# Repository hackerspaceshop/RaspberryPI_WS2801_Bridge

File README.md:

RaspberryPI_WS2801_Bridge
=========================

Software for Raspberry PI to WS2801 Bridge 
/pcb  folder includes latest schematic and baord file (eagle)  + pdf
/software includes all the raspberry pi software
/image contains one big image file that you can directly dd to an SD card (min 4GB)

http://www.hackerspaceshop.com/ledstrips/raspberrypi-ws2801.html

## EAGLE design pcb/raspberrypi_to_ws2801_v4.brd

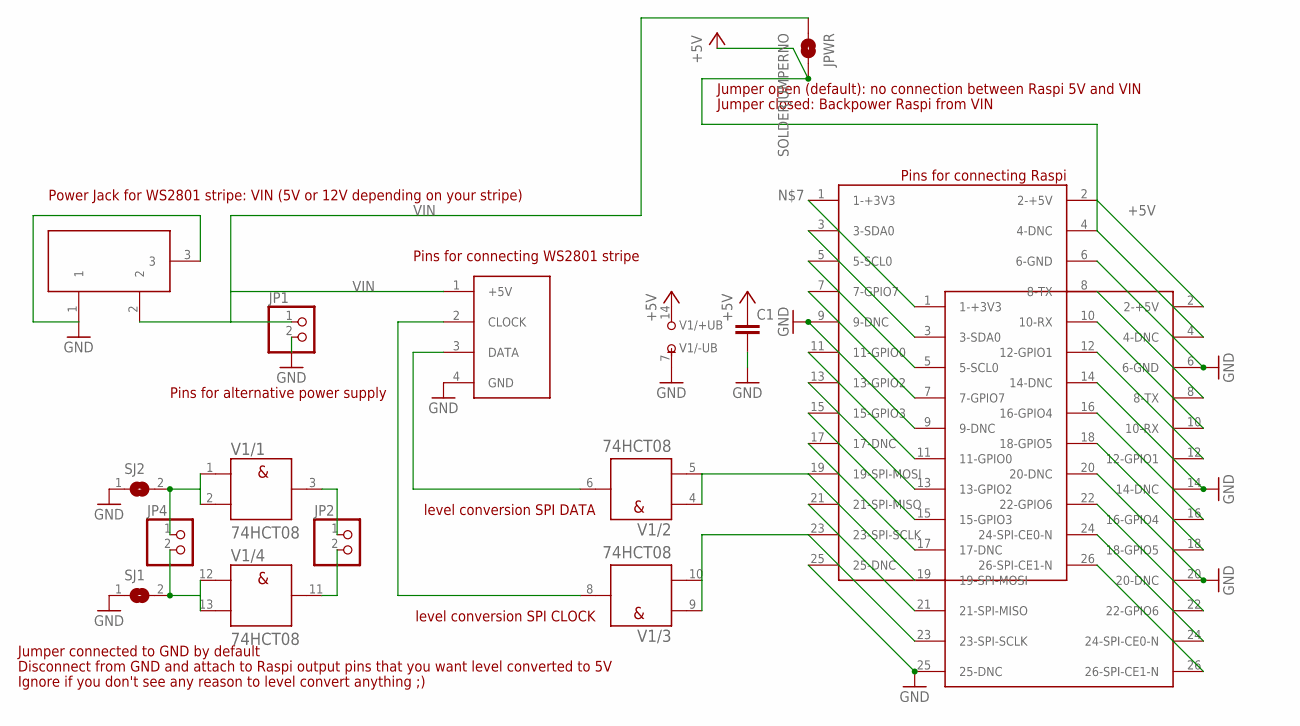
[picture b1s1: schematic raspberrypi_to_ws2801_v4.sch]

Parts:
C1: C-EU025-024X044; C025-024X044
JP1, JP2, JP4: PINHD-1X2; 1X02
JPWR: SOLDERJUMPERNO; SJ_2S-NO
SJ1, SJ2: SJ
U$1, U$2: RASPBERRY-PI
U$3: W2801STRIP; 1X04
U$5: DC21MMX; DC-21MM
V1: 74HCT08; DIL14

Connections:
+5V: C1.1, JPWR.2, U$1.2 (2-+5V), U$1.4 (4-DNC), U$2.2 (2-+5V), U$2.4 (4-DNC), V1.14 (+UB)
GND: C1.2, JP1.2, SJ1.1, SJ2.1, U$1.6 (6-GND), U$1.9 (9-DNC), U$1.14 (14-DNC), U$1.20 (20-DNC), U$1.25 (25-DNC), U$2.6 (6-GND), U$2.9 (9-DNC), U$2.14 (14-DNC), U$2.20 (20-DNC), U$2.25 (25-DNC), U$3.4 (GND), U$5.1, U$5.3, V1.7 (-UB)
unnamed: U$1.19 (19-SPI-MOSI), U$2.19 (19-SPI-MOSI), V1.4 (A), V1.5 (B)
unnamed: U$3.2 (CLOCK), V1.8 (Y)
unnamed: U$1.23 (23-SPI-SCLK), U$2.23 (23-SPI-SCLK), V1.9 (A), V1.10 (B)
unnamed: U$1.3 (3-SDA0), U$2.3 (3-SDA0)
unnamed: U$1.5 (5-SCL0), U$2.5 (5-SCL0)
unnamed: U$1.1 (1-+3V3), U$2.1 (1-+3V3)
unnamed: U$1.7 (7-GPIO7), U$2.7 (7-GPIO7)
unnamed: U$1.8 (8-TX), U$2.8 (8-TX)
unnamed: U$1.10 (10-RX), U$2.10 (10-RX)
unnamed: U$1.11 (11-GPIO0), U$2.11 (11-GPIO0)
unnamed: U$1.12 (12-GPIO1), U$2.12 (12-GPIO1)
unnamed: U$1.13 (13-GPIO2), U$2.13 (13-GPIO2)
unnamed: U$1.15 (15-GPIO3), U$2.15 (15-GPIO3)
unnamed: U$1.16 (16-GPIO4), U$2.16 (16-GPIO4)
unnamed: U$1.17 (17-DNC), U$2.17 (17-DNC)
unnamed: U$1.18 (18-GPIO5), U$2.18 (18-GPIO5)
unnamed: U$1.21 (21-SPI-MISO), U$2.21 (21-SPI-MISO)
unnamed: U$1.22 (22-GPIO6), U$2.22 (22-GPIO6)
unnamed: U$1.24 (24-SPI-CE0-N), U$2.24 (24-SPI-CE0-N)
unnamed: U$1.26 (26-SPI-CE1-N), U$2.26 (26-SPI-CE1-N)
unnamed: U$3.3 (DATA), V1.6 (Y)
unnamed: JP2.1, V1.3 (Y)
unnamed: JP2.2, V1.11 (Y)
unnamed: JP4.2, SJ1.2, V1.12 (A), V1.13 (B)
unnamed: JP4.1, SJ2.2, V1.1 (A), V1.2 (B)
VIN: JP1.1, JPWR.1, U$3.1 (+5V), U$5.2

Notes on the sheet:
Jumper connected to GND by default
Jumper open (default): no connection between Raspi 5V and VIN
Power Jack for WS2801 stripe: VIN (5V or 12V depending on your stripe)
Disconnect from GND and attach to Raspi output pins that you want level converted to 5V
Jumper closed: Backpower Raspi from VIN
Pins for alternative power supply
Pins for connecting WS2801 stripe
Pins for connecting Raspi
level conversion SPI DATA
level conversion SPI CLOCK
Ignore if you don't see any reason to level convert anything ;)

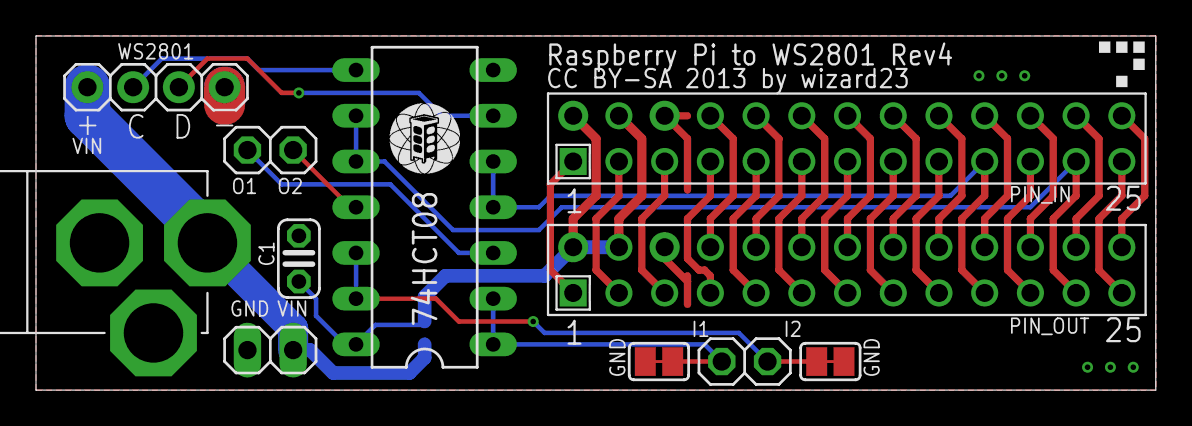
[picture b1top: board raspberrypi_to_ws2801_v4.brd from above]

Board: 2 copper layers, 62.2 x 19.7 mm, 13 parts (1 on the bottom side), 28 nets.

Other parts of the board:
U$4: METALAB_SMALL

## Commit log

2013-03-19 Wrote initial library and demo
2013-03-22 added scematic and pcb with comments :)
2013-06-12 added schemativ .pdf
2013-09-26 added v4 schematic and SDcard image, software ported to spidev
2013-09-26 added spidev.so from py-spi
2013-10-04 Added a missing letter on command
2013-11-10 whitespace python files
    and some pep8 stylin'
2013-11-10 refactor library use some basic inheritance
2013-11-10 update file based backend to have same argument order
2013-11-10 convert comments to docstrings
2013-11-10 update demo to take number of leds as an argument
2013-11-10 update demo to wrap entrypoint logic in __main__
2013-11-10 fix 'fillAll' assumed led count of 25
2014-01-10 Added Old Filebased (non SPI) import for backwards compatibility
2014-02-19 Added knight rider demo

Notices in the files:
pcb/raspberrypi_to_ws2801_v4.brd:
CC BY-SA 2013 by wizard23
parts and their libraries:
SparkFun-Passives: Licensing: CC v3.0 Share-Alike You are welcome to use this library for commercial purposes.
